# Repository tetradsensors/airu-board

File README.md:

# airu-board

This repo hold the AirU PCB

## AirU PoE board note:
The AirU PoE board connects GPIO12 to a pull-up resistor, which automatically sets the flash voltage to 1.8v. In order to use this firmware, the VDD_SDIO efuse of the ESP32 must be set using the following command:
```
espefuse.py set_flash_voltage 3.3V
```

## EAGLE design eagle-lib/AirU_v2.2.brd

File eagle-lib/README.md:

# AirU_PoE Schematic and Layout

Last Modified: October 30, 2019 by Henry Gilbert

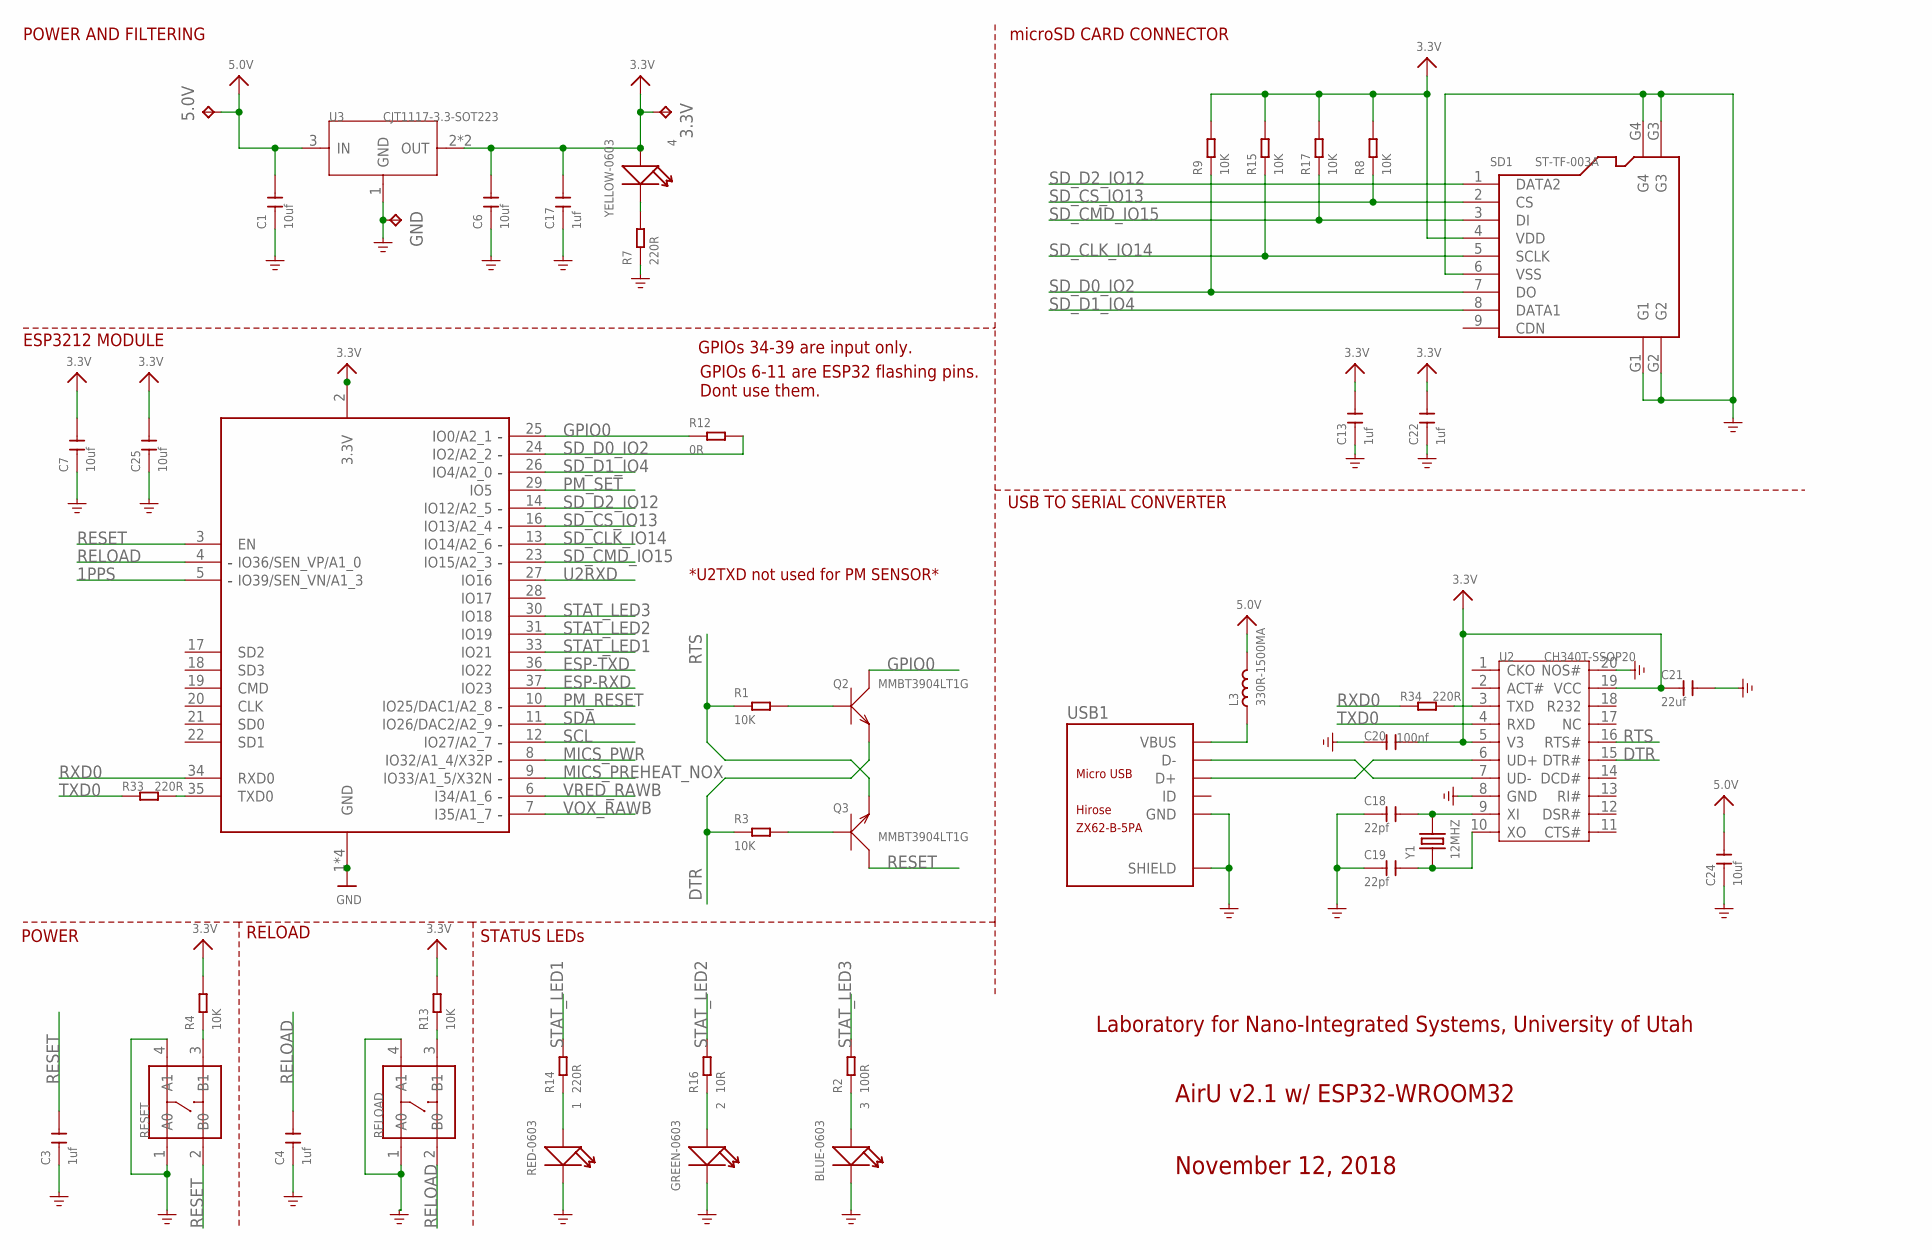
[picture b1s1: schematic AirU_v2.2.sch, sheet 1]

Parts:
1: RED-0603; LED-0603
2: GREEN-0603; LED-0603
3: BLUE-0603; LED-0603
3.3V, 5.0V: TPTP20SQ; TP20SQ
4: YELLOW-0603; LED-0603
C1, C6, C7, C24, C25: 10uf; C0603
C3, C4, C13, C17, C22: 1uf; C0603
C18, C19: 22pf; C0603
C20: 100nf; C0603
C21: 22uf; C0805
GND: TPTP20SQ; TP20SQ
L3: 330R-1500MA; L0805
Q2, Q3: MMBT3904LT1G; SOT-23
R1, R3, R4, R8, R9, R13, R15, R17: 10K; R0603
R2: 100R; R0603
R7, R14, R33, R34: 220R; R0603
R12: 0R; R0603
R16: 10R; R0603
RELOAD: DIP-SWITCH-TACTILE-SPST-NO/TS-1109(4P-D6.0MM)'TS-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; SW4-6.0X6.0X5.0MM
RESET: DIP-SWITCH-TACTILE-SPST-NO/TS-1109(4P-D6.0MM)'TS-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; SW4-6.0X6.0X5.0MM
SD1: ST-TF-003A; MICRO-SD9+4P-SMD-16.1X14.5X1.85MM
U2: CH340T-SSOP20; SSOP20-0.65-7.6X5.2MM
U3: CJT1117-3.3-SOT223; SOT-223
U7: ESP32_WROOM32_SKINNY; WROOM32_SKINNY
USB1: ZX62-B-5PA; MICRO-USB5+6P-SMD-0.65-AB
Y1: 12MHZ; X2-SMD-5.0X3.2X1.3MM

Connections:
1PPS: U7.5 (IO39/SEN_VN/A1_3); also elsewhere on the board
3.3V: 3.3V.TP, 4.+, C6.2, C7.2, C13.2, C17.2, C20.2, C21.1, C22.2, C25.2, R4.2, R8.2, R9.2, R13.2, R15.2, R17.2, SD1.4 (VDD), U2.5 (V3), U2.19 (VCC), U3.2 (OUT), U3.TER (OUT), U7.2 (3.3V); also elsewhere on the board
5.0V: 5.0V.TP, C1.2, C24.2, L3.2, U3.3 (IN); also elsewhere on the board
DTR: Q2.2 (E), R3.1, U2.15 (DTR#)
ESP-RXD: U7.37 (IO23); also elsewhere on the board
ESP-TXD: U7.36 (IO22); also elsewhere on the board
GND: 1.-, 2.-, 3.-, C1.1, C3.1, C4.1, C6.1, C7.1, C13.1, C17.1, C18.1, C19.1, C20.1, C21.2, C22.1, C24.1, C25.1, GND.TP, R7.1, RELOAD.1 (A0), RELOAD.4 (A1), RESET.1 (A0), RESET.4 (A1), SD1.6 (VSS), SD1.G1, SD1.G2, SD1.G3, SD1.G4, U2.8 (GND), U2.20 (NOS#), U3.1 (GND), U7.1 (GND), U7.15 (GND), U7.38 (GND), U7.P$1 (GND), USB1.5 (GND), USB1.P1 (SHIELD), USB1.P2 (SHIELD), USB1.P3_1 (SHIELD), USB1.P3_2 (SHIELD), USB1.P3_3 (SHIELD), USB1.P4_1 (SHIELD), USB1.P4_2 (SHIELD), USB1.P4_3 (SHIELD), USB1.P5 (SHIELD), USB1.P6 (SHIELD); also elsewhere on the board
GPIO0: Q2.3 (C), R12.1, U7.25 (IO0/A2_1)
MICS_PREHEAT_NOX: U7.9 (IO33/A1_5/X32N); also elsewhere on the board
MICS_PWR: U7.8 (IO32/A1_4/X32P); also elsewhere on the board
unnamed: 2.+, R16.1
unnamed: 1.+, R14.1
unnamed: Q3.1 (B), R3.2
unnamed: Q2.1 (B), R1.2
unnamed: 3.+, R2.1
unnamed: 4.-, R7.2
unnamed: U2.7 (UD-), USB1.2 (D-)
unnamed: U2.6 (UD+), USB1.3 (D+)
unnamed: C18.2, U2.9 (XI), Y1.2
unnamed: C19.2, U2.10 (XO), Y1.1
unnamed: R34.2, U2.3 (TXD)
unnamed: R33.2, U7.35 (TXD0)
unnamed: R13.1, RELOAD.3 (B1)
unnamed: R4.1, RESET.3 (B1)
PM_RESET: U7.10 (IO25/DAC1/A2_8); also elsewhere on the board
PM_SET: U7.29 (IO5); also elsewhere on the board
RELOAD: C4.2, RELOAD.2 (B0), U7.4 (IO36/SEN_VP/A1_0)
RESET: C3.2, Q3.3 (C), RESET.2 (B0), U7.3 (EN)
RTS: Q3.2 (E), R1.1, U2.16 (RTS#)
RXD0: R34.1, U7.34 (RXD0)
SCL: U7.12 (IO27/A2_7); also elsewhere on the board
SDA: U7.11 (IO26/DAC2/A2_9); also elsewhere on the board
SD_CLK_IO14: R15.1, SD1.5 (SCLK), U7.13 (IO14/A2_6)
SD_CMD_IO15: R17.1, SD1.3 (DI), U7.23 (IO15/A2_3)
SD_CS_IO13: R8.1, SD1.2 (CS), U7.16 (IO13/A2_4)
SD_D0_IO2: R9.1, R12.2, SD1.7 (DO), U7.24 (IO2/A2_2)
SD_D1_IO4: SD1.8 (DATA1), U7.26 (IO4/A2_0)
SD_D2_IO12: SD1.1 (DATA2), U7.14 (IO12/A2_5)
STAT_LED1: R14.2, U7.33 (IO21)
STAT_LED2: R16.2, U7.31 (IO19)
STAT_LED3: R2.2, U7.30 (IO18)
TXD0: R33.1, U2.4 (RXD)
U2RXD: U7.27 (IO16); also elsewhere on the board
VBUS: L3.1, USB1.1 (VBUS)
VOX_RAWB: U7.7 (I35/A1_7); also elsewhere on the board
VRED_RAWB: U7.6 (I34/A1_6); also elsewhere on the board

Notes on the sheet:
POWER AND FILTERING
RELOAD
USB TO SERIAL CONVERTER
ESP3212 MODULE
POWER
microSD CARD CONNECTOR
AirU v2.1 w/ ESP32-WROOM32
November 12, 2018
STATUS LEDs
*U2TXD not used for PM SENSOR*
GPIOs 34-39 are input only.
Laboratory for Nano-Integrated Systems, University of Utah
GPIOs 6-11 are ESP32 flashing pins. Dont use them.

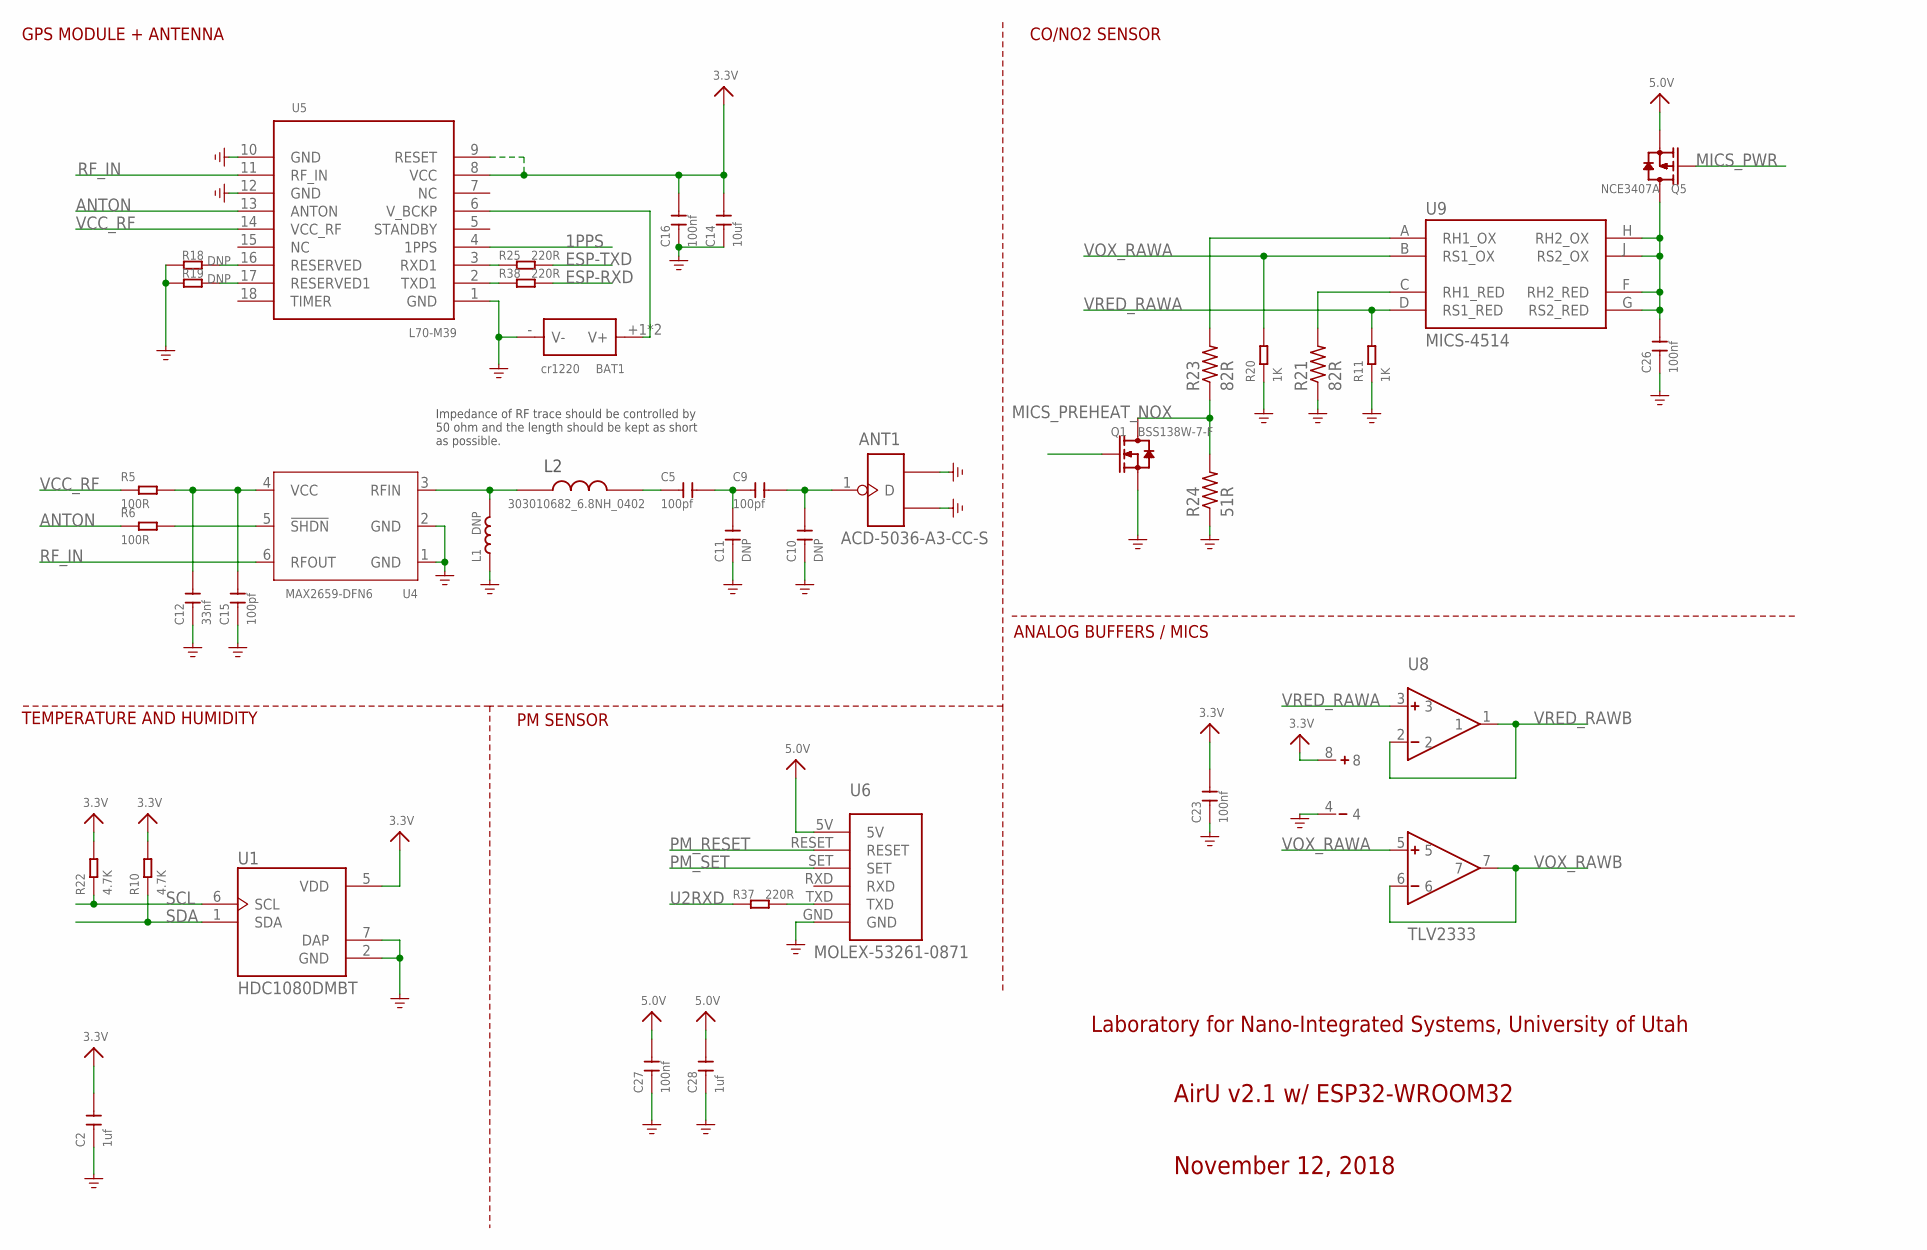
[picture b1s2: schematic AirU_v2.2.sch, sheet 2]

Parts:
ANT1: ACD-5036-A3-CC-S; ANT3-SMD-5.2X3.7X0.7MM
BAT1: cr1220; BAT2P-13.5-CR1220
C2, C28: 1uf; C0603
C5, C9, C15: 100pf; C0603
C10, C11: DNP; C0603
C12: 33nf; C0603
C14: 10uf; C0603
C16, C23, C26, C27: 100nf; C0603
L1: DNP; L0201
L2: 303010682_6.8NH_0402; L0402
Q1: BSS138W-7-F; SOT-23
Q5: NCE3407A; SOT-23
R5, R6: 100R; R0603
R10, R22: 4.7K; R0603
R11, R20: 1K; R0603
R18, R19: DNP; R0603
R21, R23: 82R; R0603
R24: 51R; R0603
R25, R37, R38: 220R; R0603
U1: HDC1080DMBT; SON100P300X300X80-7N
U4: MAX2659-DFN6; DFN6-0.5-1.5X1.2X0.72MM
U5: L70-M39; LGA18-1.1-9.7X10.1X2.5MM
U6: MOLEX-53261-0871
U8: TLV2333
U9: MICS-4514; MICS_10-SMD

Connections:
1PPS: U5.4 (1PPS); also elsewhere on the board
3.3V: C2.2, C14.2, C16.2, C23.2, R10.2, R22.2, U1.5 (VDD), U5.8 (VCC), U5.9 (RESET), U8.8; also elsewhere on the board
5.0V: C27.2, C28.2, Q5.2 (S), U6.5V; also elsewhere on the board
ANTON: R6.1, U5.13 (ANTON)
ESP-RXD: R38.2; also elsewhere on the board
ESP-TXD: R25.2; also elsewhere on the board
GND: ANT1.2 (GND1), ANT1.3 (GND2), BAT1.- (V-), C2.1, C10.1, C11.1, C12.1, C14.1, C15.1, C16.1, C23.1, C26.1, C27.1, C28.1, L1.1, Q1.2 (S), R11.1, R18.1, R19.1, R20.1, R21.1, R24.1, U1.2 (GND), U1.7 (DAP), U4.1 (GND), U4.2 (GND), U5.1 (GND), U5.10 (GND), U5.12 (GND), U6.GND, U8.4; also elsewhere on the board
MICS_PREHEAT_NOX: Q1.1 (G); also elsewhere on the board
MICS_PWR: Q5.1 (G); also elsewhere on the board
unnamed: R21.2, U9.C (RH1_RED)
unnamed: C5.2, C9.1, C11.2
unnamed: ANT1.1 (D), C9.2, C10.2
unnamed: L1.2, L2.P$1, U4.3 (RFIN)
unnamed: R23.2, U9.A (RH1_OX)
unnamed: C5.1, L2.P$2
unnamed: R6.2, U4.5 (!SHDN)
unnamed: C12.2, C15.2, R5.2, U4.4 (VCC)
unnamed: R18.2, U5.16 (RESERVED)
unnamed: R19.2, U5.17 (RESERVED1)
unnamed: Q1.3 (D), R23.1, R24.2
unnamed: C26.2, Q5.3 (D), U9.F (RH2_RED), U9.G (RS2_RED), U9.H (RH2_OX), U9.J (RS2_OX)
unnamed: R37.2, U6.TXD
PM_RESET: U6.RESET; also elsewhere on the board
PM_SET: U6.SET; also elsewhere on the board
RF_IN: U4.6 (RFOUT), U5.11 (RF_IN)
SCL: R22.1, U1.6 (SCL); also elsewhere on the board
SDA: R10.1, U1.1 (SDA); also elsewhere on the board
U1RXD: R25.1, U5.3 (RXD1)
U1TXD: R38.1, U5.2 (TXD1)
U2RXD: R37.1; also elsewhere on the board
VCC_RF: R5.1, U5.14 (VCC_RF)
VOX_RAWA: R20.2, U8.5, U9.B (RS1_OX)
VOX_RAWB: U8.6, U8.7; also elsewhere on the board
VRED_RAWA: R11.2, U8.3, U9.D (RS1_RED)
VRED_RAWB: U8.1, U8.2; also elsewhere on the board
V_BCKP: BAT1.+1 (V+), BAT1.+2 (V+), U5.6 (V_BCKP)

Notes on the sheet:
PM SENSOR
Impedance of RF trace should be controlled by 50 ohm and the length should be kept as short as possible.
TEMPERATURE AND HUMIDITY
GPS MODULE + ANTENNA
CO/NO2 SENSOR
AirU v2.1 w/ ESP32-WROOM32
November 12, 2018
ANALOG BUFFERS / MICS
Laboratory for Nano-Integrated Systems, University of Utah

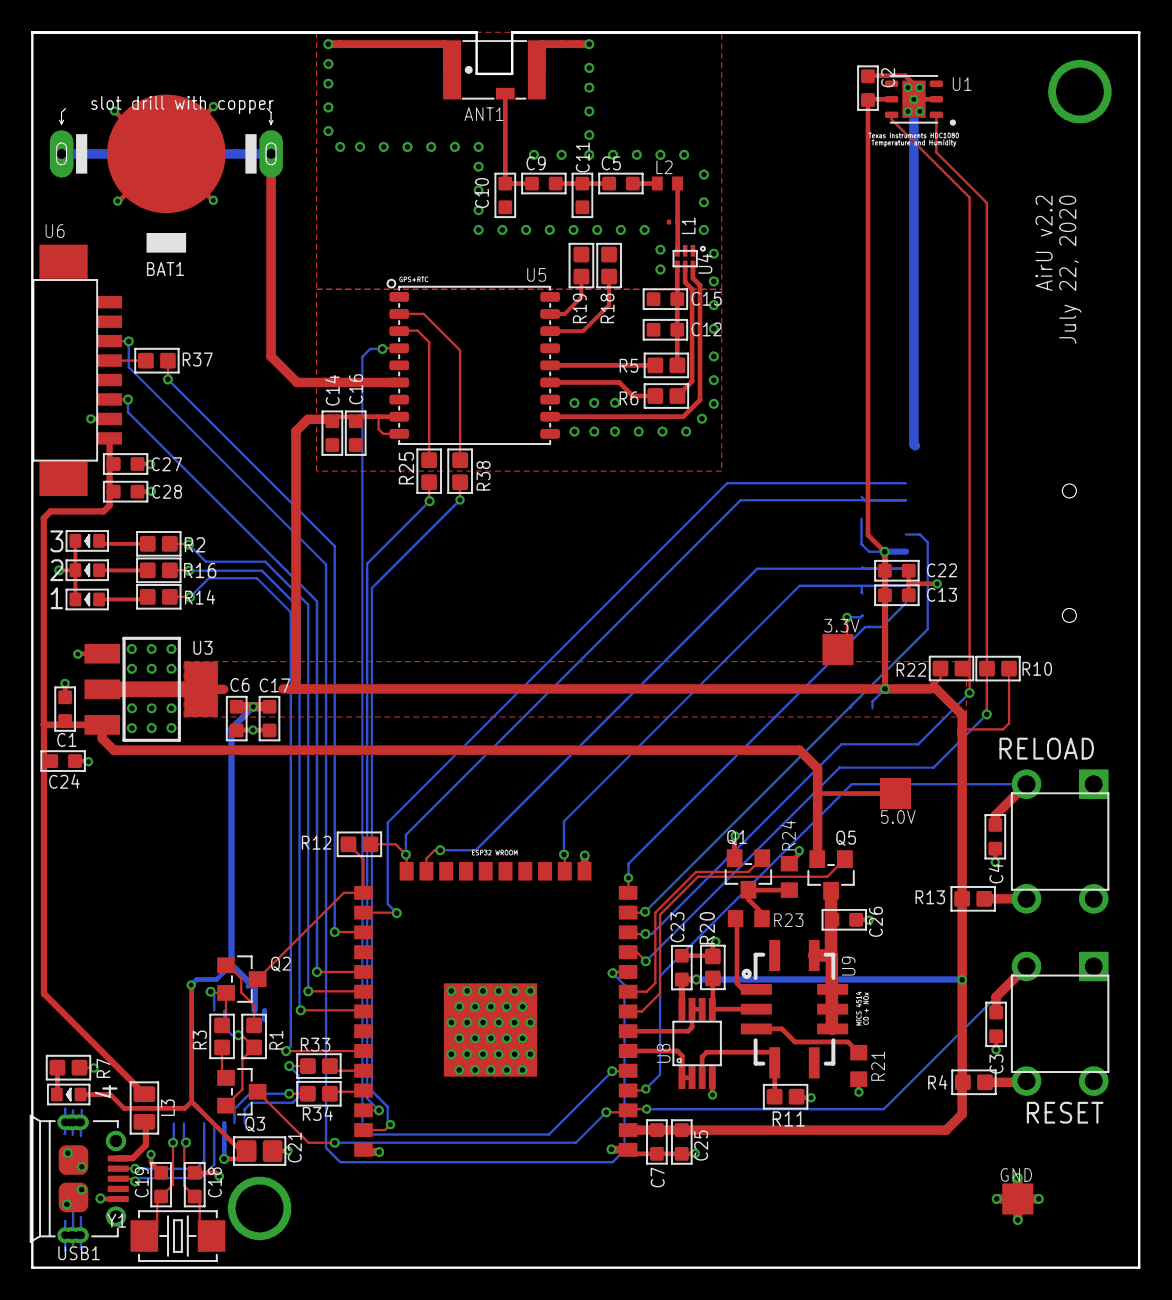
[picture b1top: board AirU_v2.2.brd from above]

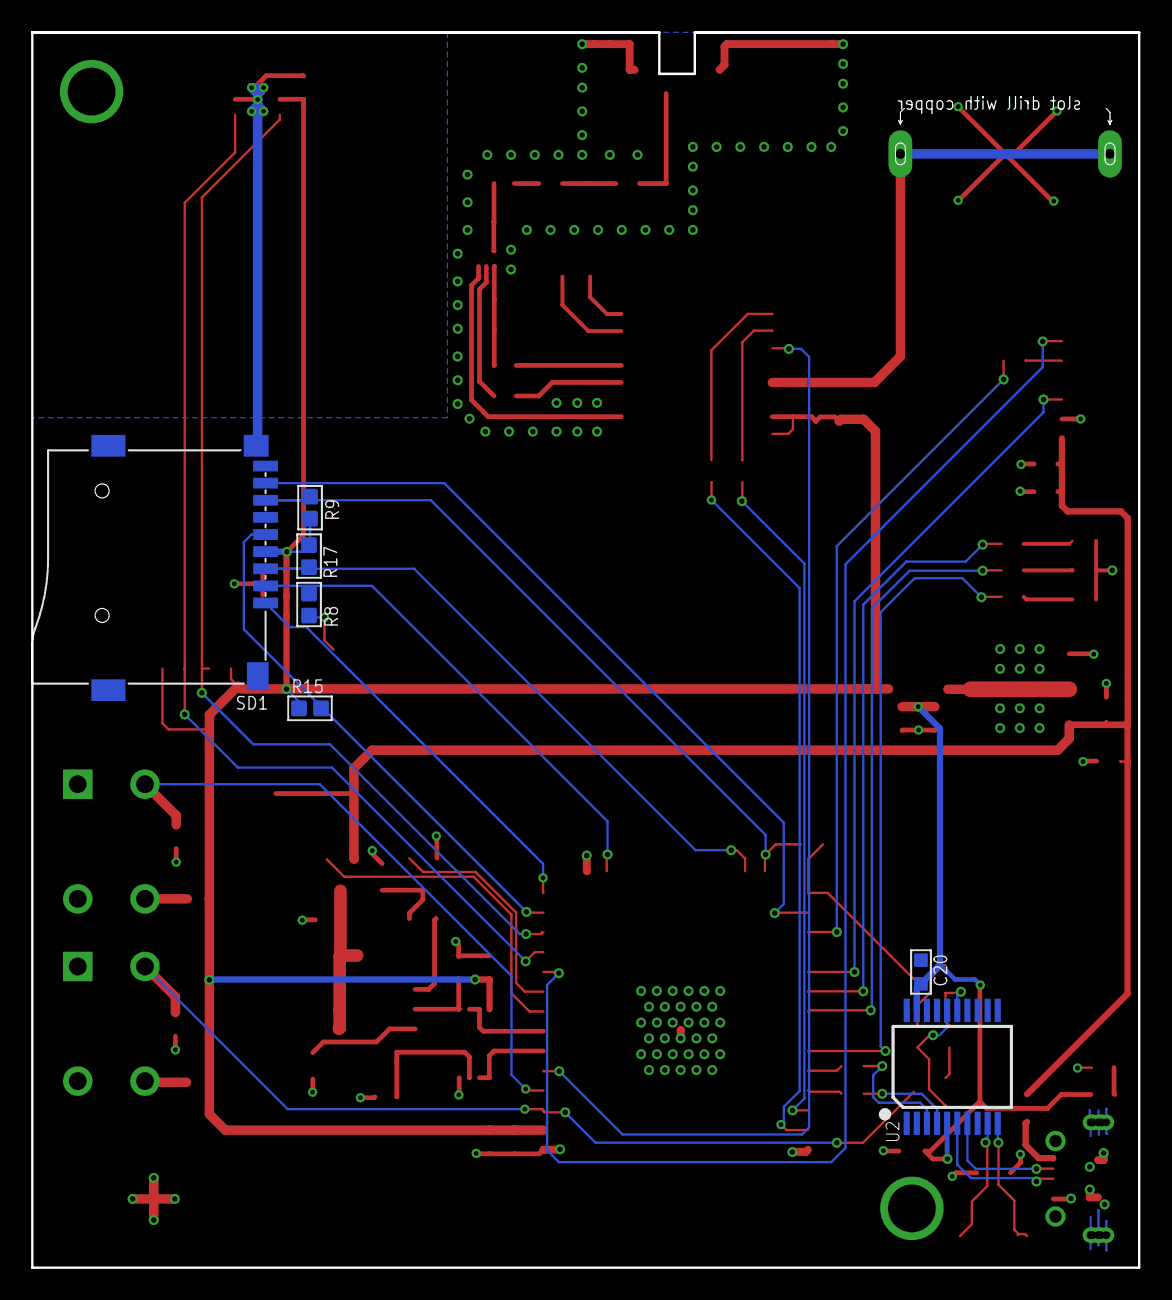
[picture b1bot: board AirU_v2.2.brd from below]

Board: 2 copper layers, 71.1 x 79.4 mm, 86 parts (7 on the bottom side), 67 nets.

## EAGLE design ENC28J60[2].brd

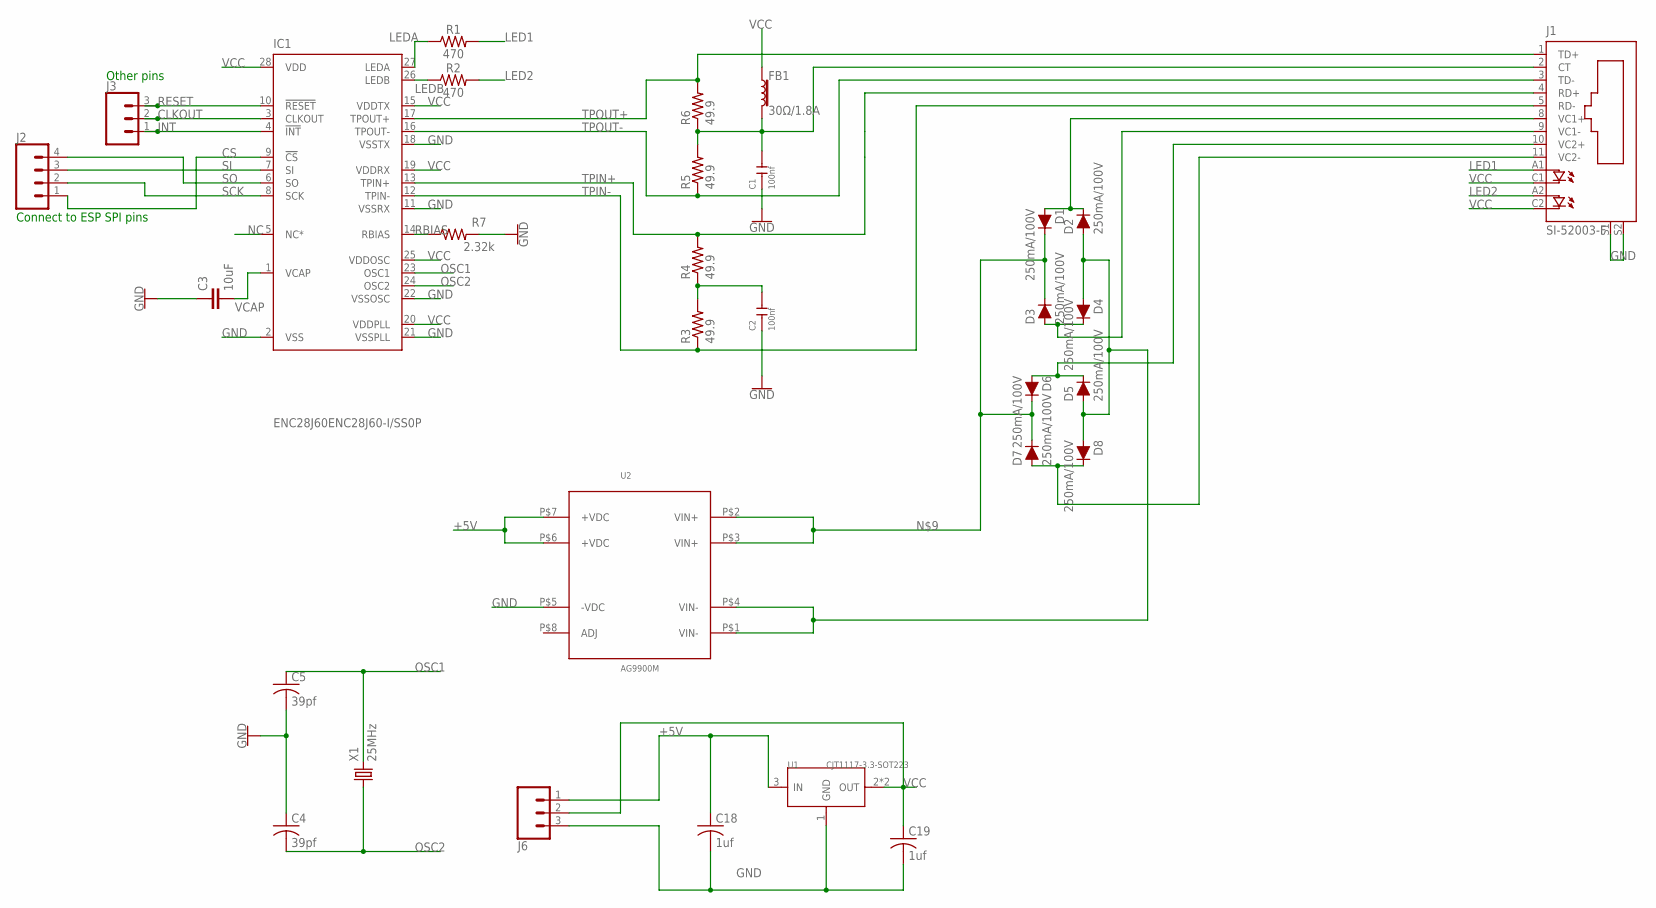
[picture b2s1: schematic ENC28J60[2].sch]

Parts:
C1, C2: 100nf; C0603
C3: 10uF; 0805
C4, C5: 39pf; C0402
C18, C19: 1uf; C0402
D1, D2, D3, D4, D5, D6, D7, D8: 250mA/100V; SOD-323
FB1: 30Ω/1.8A; 0603
IC1: ENC28J60ENC28J60-I/SS0P; SOP65P780X200-28
J1: SI-52003-F
J2: CONN_04; 1X04
J3, J6: CONN_03; 1X03
R1, R2: 470; 0603
R3, R4, R5, R6: 49.9; M0805
R7: 2.32k; 0603
U1: CJT1117-3.3-SOT223; SOT-223
U2: AG9900M; AG9900M/MT
X1: 25MHz; XTALRR488W48L1067T422H350B

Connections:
+5V: C18.1, J6.1, U1.3 (IN), U2.P$6 (+VDC), U2.P$7 (+VDC)
CLKOUT: IC1.3 (CLKOUT), J3.2
CS: IC1.9 (!CS), J2.1
GND: C1.1, C2.1, C3.1, C4.1, C5.2, C18.2, C19.2, IC1.2 (VSS), IC1.11 (VSSRX), IC1.18 (VSSTX), IC1.21 (VSSPLL), IC1.22 (VSSOSC), J1.S1, J1.S2, J6.3, R7.2, U1.1 (GND), U2.P$5 (-VDC)
INT: IC1.4 (!INT), J3.1
LED1: J1.A1, R1.2
LED2: J1.A2, R2.2
LEDA: IC1.27 (LEDA), R1.1
LEDB: IC1.26 (LEDB), R2.1
unnamed: D3.A, D4.C, J1.9 (VC1-)
unnamed: D7.A, D8.C, J1.11 (VC2-)
unnamed: C1.2, FB1.2, J1.2 (CT), R5.2, R6.1
unnamed: D1.A, D2.C, J1.8 (VC1+)
unnamed: D1.C, D3.C, D6.C, D7.C, U2.P$2 (VIN+), U2.P$3 (VIN+)
unnamed: D5.C, D6.A, J1.10 (VC2+)
unnamed: C2.2, R3.2, R4.1
unnamed: D2.A, D4.A, D5.A, D8.A, U2.P$1 (VIN-), U2.P$4 (VIN-)
NC: IC1.5 (NC*)
OSC1: C5.1, IC1.23 (OSC1), X1.2
OSC2: C4.2, IC1.24 (OSC2), X1.1
RBIAS: IC1.14 (RBIAS), R7.1
RESET: IC1.10 (!RESET), J3.3
SCK: IC1.8 (SCK), J2.2
SI: IC1.7 (SI), J2.3
SO: IC1.6 (SO), J2.4
TPIN+: IC1.13 (TPIN+), J1.4 (RD+), R4.2
TPIN-: IC1.12 (TPIN-), J1.5 (RD-), R3.1
TPOUT+: IC1.17 (TPOUT+), J1.1 (TD+), R6.2
TPOUT-: IC1.16 (TPOUT-), J1.3 (TD-), R5.1
VCAP: C3.2, IC1.1 (VCAP)
VCC: C19.1, FB1.1, IC1.15 (VDDTX), IC1.19 (VDDRX), IC1.20 (VDDPLL), IC1.25 (VDDOSC), IC1.28 (VDD), J1.C1, J1.C2, J6.2, U1.2 (OUT), U1.TER (OUT)

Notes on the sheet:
Connect to ESP SPI pins
Other pins

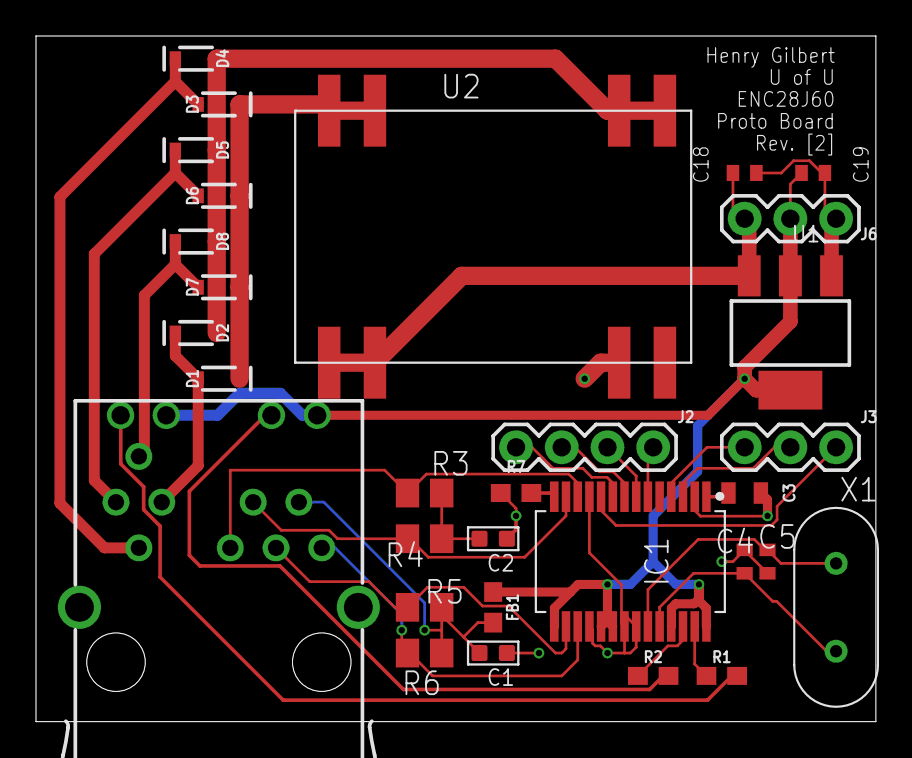
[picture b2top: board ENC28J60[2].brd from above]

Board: 2 copper layers, 46.7 x 38.1 mm, 31 parts (0 on the bottom side), 30 nets.

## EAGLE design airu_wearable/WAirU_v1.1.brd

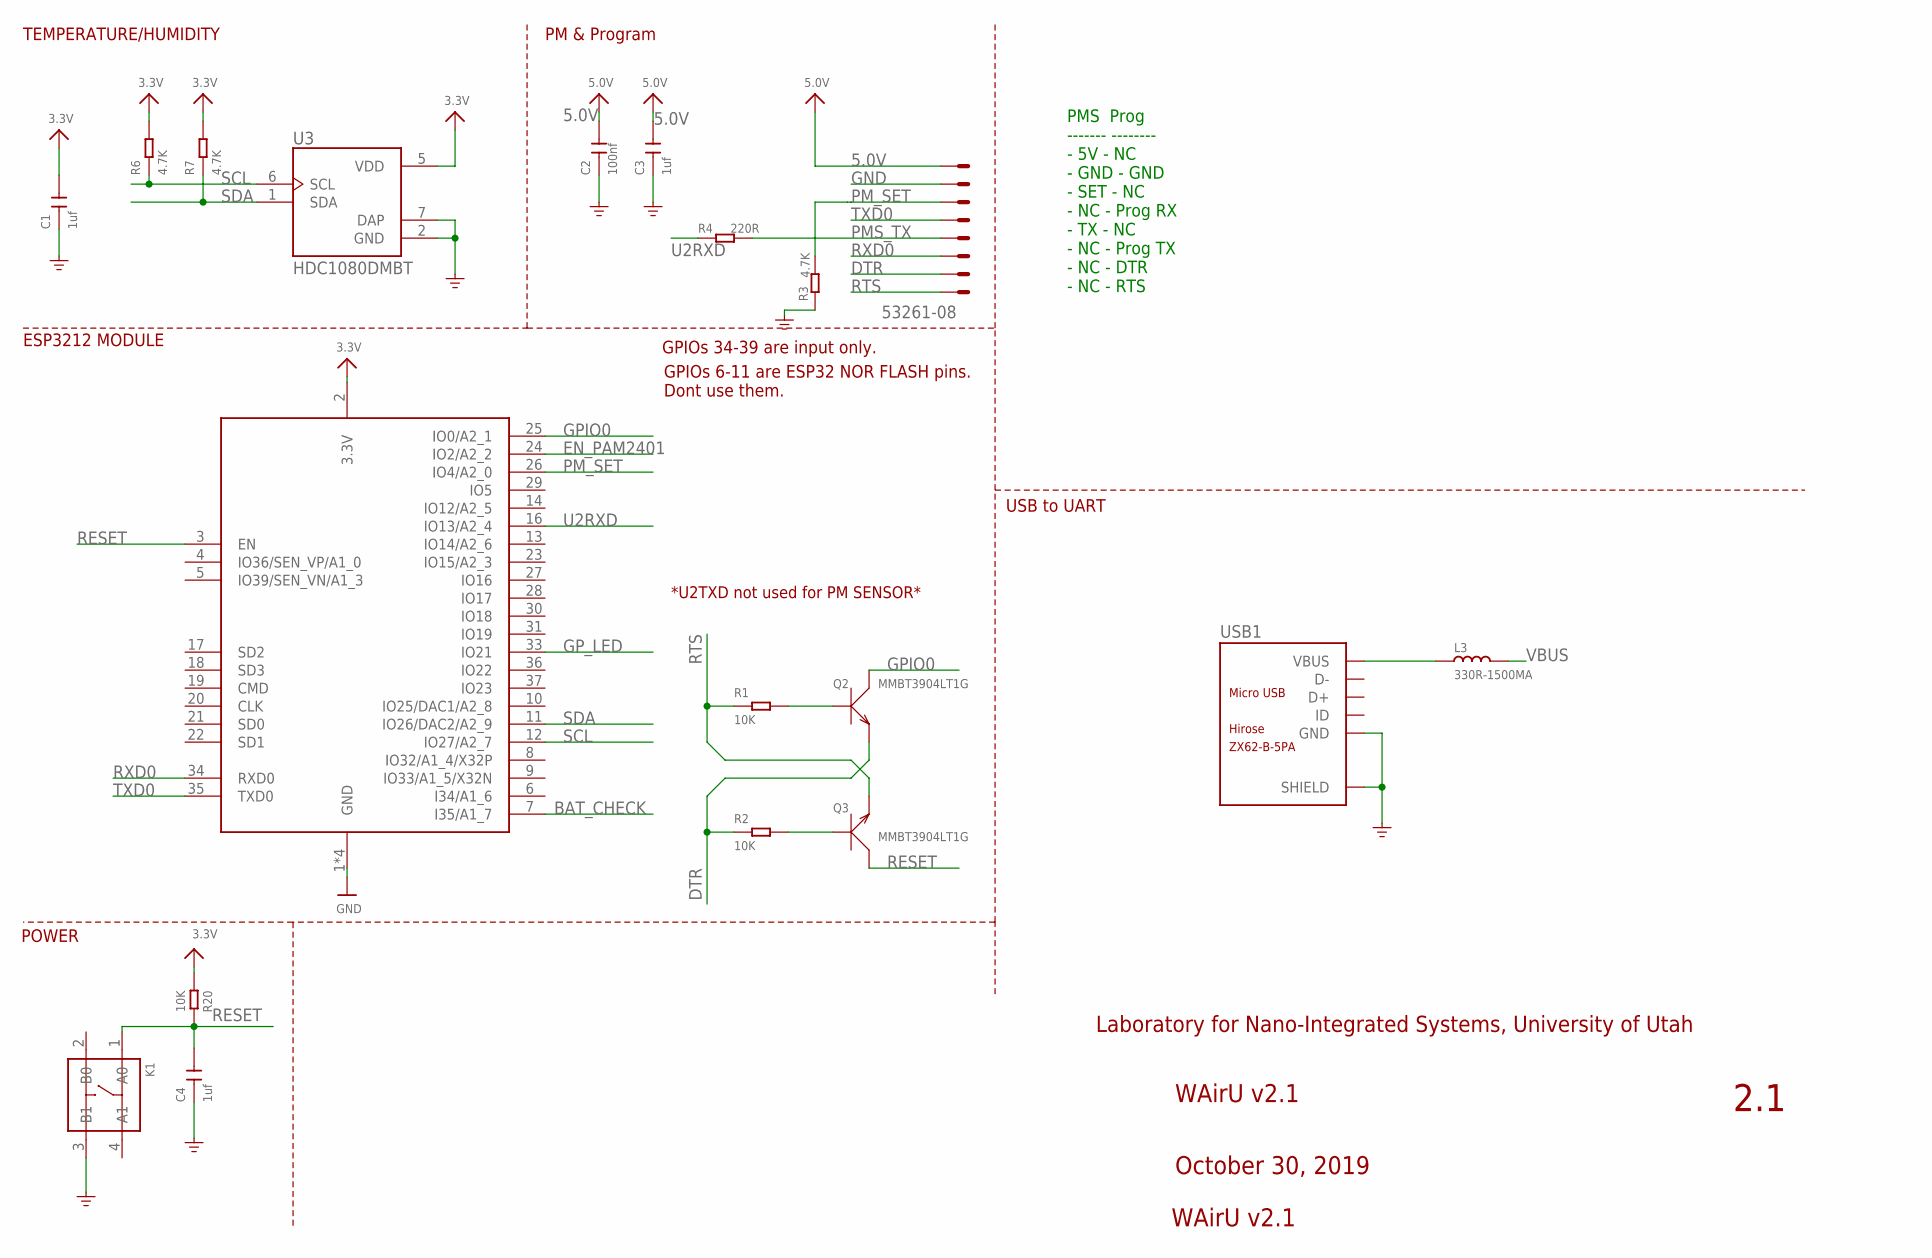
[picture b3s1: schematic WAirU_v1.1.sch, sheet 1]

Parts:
C1, C3, C4: 1uf; C0603
C2: 100nf; C0603
K1: SMD-SWITCH-TACTILE-SPST-NO(4P-D6.0MM); SW4-SMD-6.0X6.0X5.0MM
L3: 330R-1500MA; L0805
MOLEX-53261-0871: 53261-08
Q2, Q3: MMBT3904LT1G; SOT-23
R1, R2, R20: 10K; R0603
R3, R6, R7: 4.7K; R0603
R4: 220R; R0603
U3: HDC1080DMBT; SON100P300X300X80-7N
U7: ESP32_WROOM32_SKINNY; WROOM32_SKINNY
USB1: ZX62-B-5PA; MICRO-USB5+6P-SMD-0.65-AB

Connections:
3.3V: C1.2, R6.2, R7.2, R20.1, U3.5 (VDD), U7.2 (3.3V); also elsewhere on the board
5.0V: C2.2, C3.2, MOLEX-53261-0871.8; also elsewhere on the board
BAT_CHECK: U7.7 (I35/A1_7); also elsewhere on the board
DTR: MOLEX-53261-0871.2, Q2.2 (E), R2.1
EN_PAM2401: U7.24 (IO2/A2_2); also elsewhere on the board
GND: C1.1, C2.1, C3.1, C4.1, K1.3 (B1), MOLEX-53261-0871.7, R3.1, U3.2 (GND), U3.7 (DAP), U7.1 (GND), U7.15 (GND), U7.38 (GND), U7.P$1 (GND), USB1.5 (GND), USB1.P1 (SHIELD), USB1.P2 (SHIELD), USB1.P3_1 (SHIELD), USB1.P3_2 (SHIELD), USB1.P3_3 (SHIELD), USB1.P4_1 (SHIELD), USB1.P4_2 (SHIELD), USB1.P4_3 (SHIELD), USB1.P5 (SHIELD), USB1.P6 (SHIELD); also elsewhere on the board
GPIO0: Q2.3 (C), U7.25 (IO0/A2_1)
GP_LED: U7.33 (IO21); also elsewhere on the board
unnamed: Q3.1 (B), R2.2
unnamed: Q2.1 (B), R1.2
PMS_TX: MOLEX-53261-0871.4, R4.2
PM_SET: MOLEX-53261-0871.6, R3.2, U7.26 (IO4/A2_0)
RESET: C4.2, K1.1 (A0), Q3.3 (C), R20.2, U7.3 (EN)
RTS: MOLEX-53261-0871.1, Q3.2 (E), R1.1
RXD0: MOLEX-53261-0871.3, U7.34 (RXD0)
SCL: R6.1, U3.6 (SCL), U7.12 (IO27/A2_7)
SDA: R7.1, U3.1 (SDA), U7.11 (IO26/DAC2/A2_9)
TXD0: MOLEX-53261-0871.5, U7.35 (TXD0)
U2RXD: R4.1, U7.16 (IO13/A2_4)
VBUS: L3.2; also elsewhere on the board
VBUS_RAW: L3.1, USB1.1 (VBUS)

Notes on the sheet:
ESP3212 MODULE
POWER
WAirU v2.1
October 30, 2019
*U2TXD not used for PM SENSOR*
GPIOs 34-39 are input only.
Laboratory for Nano-Integrated Systems, University of Utah
GPIOs 6-11 are ESP32 NOR FLASH pins. Dont use them.
TEMPERATURE/HUMIDITY
PM & Program
USB to UART
PMS Prog ------- -------- - 5V - NC - GND - GND - SET - NC - NC - Prog RX - TX - NC - NC - Prog TX - NC - DTR - NC - RTS
2.1

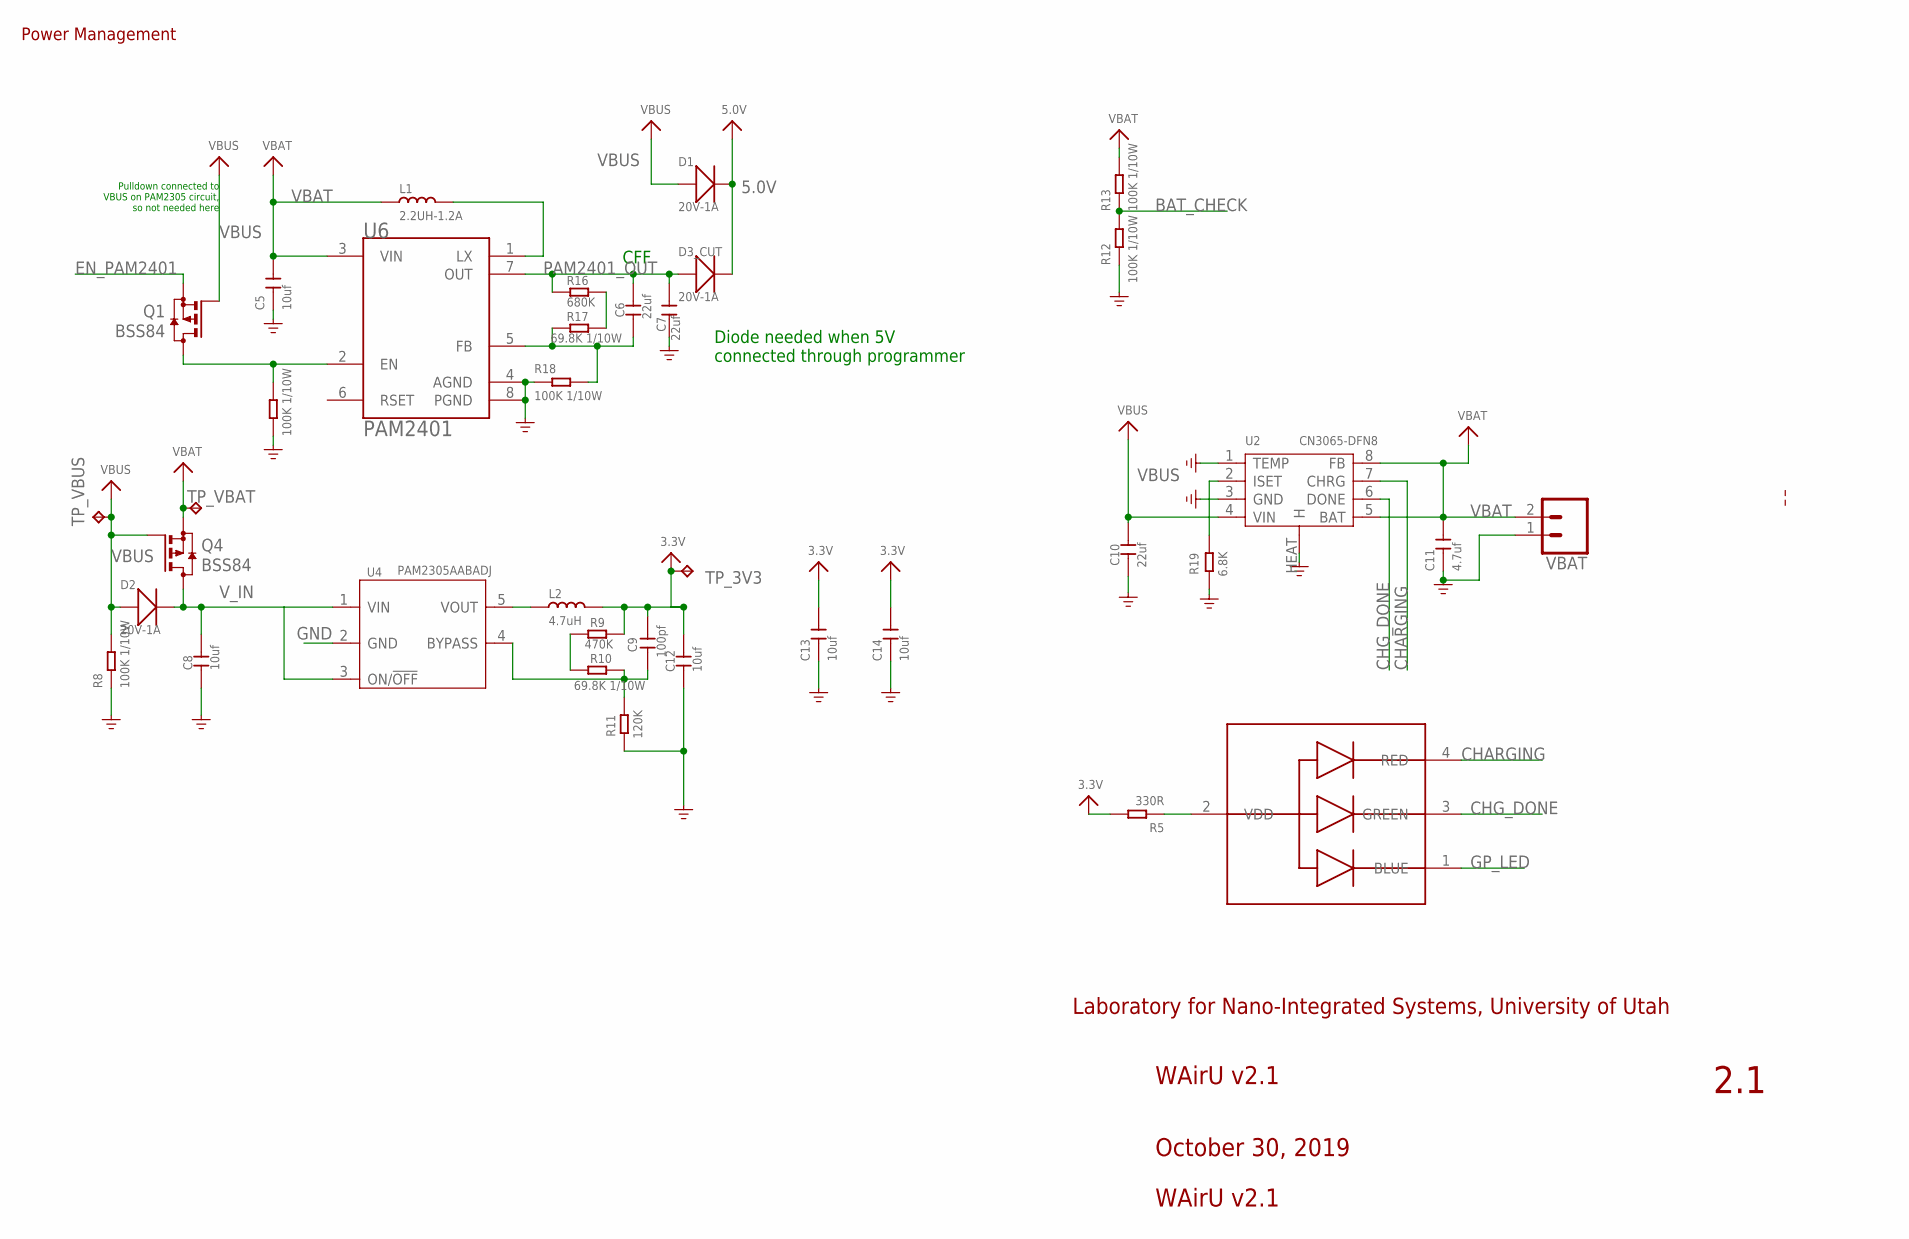
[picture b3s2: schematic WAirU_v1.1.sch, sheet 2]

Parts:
C5, C8, C12, C13, C14: 10uf; C0603
C6, C7: 22uf; C0603
C9: 100pf; C0603
C10: 22uf; C0805
C11: 4.7uf; C0603
D1, D2, D3_CUT: 20V-1A; SOD-123
L1: 2.2UH-1.2A; L0805
L2: 4.7uH; L5040S
Q1, Q4: BSS84; SOT23
R5: 330R; R0603
R8, R12, R13, R14, R18: 100K 1/10W; R0603
R9: 470K; R0603
R10, R17: 69.8K 1/10W; R0603
R11: 120K; R0603
R16: 680K; R0603
R19: 6.8K; R0603
TP_3V3: TPTP20SQ; TP20SQ
TP_VBAT: TPTP20SQ; TP20SQ
TP_VBUS: TPTP20SQ; TP20SQ
U1: 19-237A/BHR6GHC-M01/2T; SMD-19-237A
U2: CN3065-DFN8; DFN8G-0.5-3X3MM
U4: PAM2305AABADJ; SOT-23-5
U6: PAM2401; MSOP-8
VBAT: CONN_02-JST-2MM-SMT; JST-2-SMD

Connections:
3.3V: C9.2, C12.2, C13.2, C14.2, L2.2, R5.2, R9.2, TP_3V3.TP; also elsewhere on the board
5.0V: D1.-, D3_CUT.-; also elsewhere on the board
BAT_CHECK: R12.2, R13.1; also elsewhere on the board
CHARGING: U1.4 (RED), U2.7 (CHRG)
CHG_DONE: U1.3 (GREEN), U2.6 (DONE)
EN_PAM2401: Q1.2 (S); also elsewhere on the board
GND: C5.1, C7.1, C8.1, C10.1, C11.1, C12.1, C13.1, C14.1, R8.1, R11.1, R12.1, R14.1, R18.1, R19.1, U2.1 (TEMP), U2.3 (GND), U2.HEAT (H), U4.2 (GND), U6.4 (AGND), U6.8 (PGND), VBAT.1 (2); also elsewhere on the board
GP_LED: U1.1 (BLUE); also elsewhere on the board
unnamed: L1.2, U6.1 (LX)
unnamed: R19.2, U2.2 (ISET)
unnamed: Q1.3 (D), R14.2, U6.2 (EN)
unnamed: L2.1, U4.5 (VOUT)
unnamed: R5.1, U1.2 (VDD)
unnamed: C6.1, R17.1, R18.2, U6.5 (FB)
unnamed: C9.1, R10.2, R11.2, U4.4 (BYPASS)
unnamed: R16.2, R17.2
unnamed: R9.1, R10.1
PAM2401_OUT: C6.2, C7.2, D3_CUT.+, R16.1, U6.7 (OUT)
VBAT: C5.2, C11.2, L1.1, Q4.2 (S), R13.2, TP_VBAT.TP, U2.5 (BAT), U2.8 (FB), U6.3 (VIN), VBAT.2 (1)
VBUS: C10.2, D1.+, D2.+, Q1.1 (G), Q4.1 (G), R8.2, TP_VBUS.TP, U2.4 (VIN); also elsewhere on the board
V_IN: C8.2, D2.-, Q4.3 (D), U4.1 (VIN), U4.3 (ON/!OFF)

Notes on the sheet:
WAirU v2.1
October 30, 2019
Laboratory for Nano-Integrated Systems, University of Utah
CFF
Power Management
Diode needed when 5V connected through programmer
Pulldown connected to VBUS on PAM2305 circuit, so not needed here
2.1

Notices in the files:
parts and their libraries:
SparkFun-Capacitors: Licensing: Creative Commons ShareAlike 4.0 International - https://creativecommons.org/licenses/by-sa/4.0
microbuilder: This work is placed in the public domain, and may be freely used for commercial and non-commercial work with the following conditions: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
